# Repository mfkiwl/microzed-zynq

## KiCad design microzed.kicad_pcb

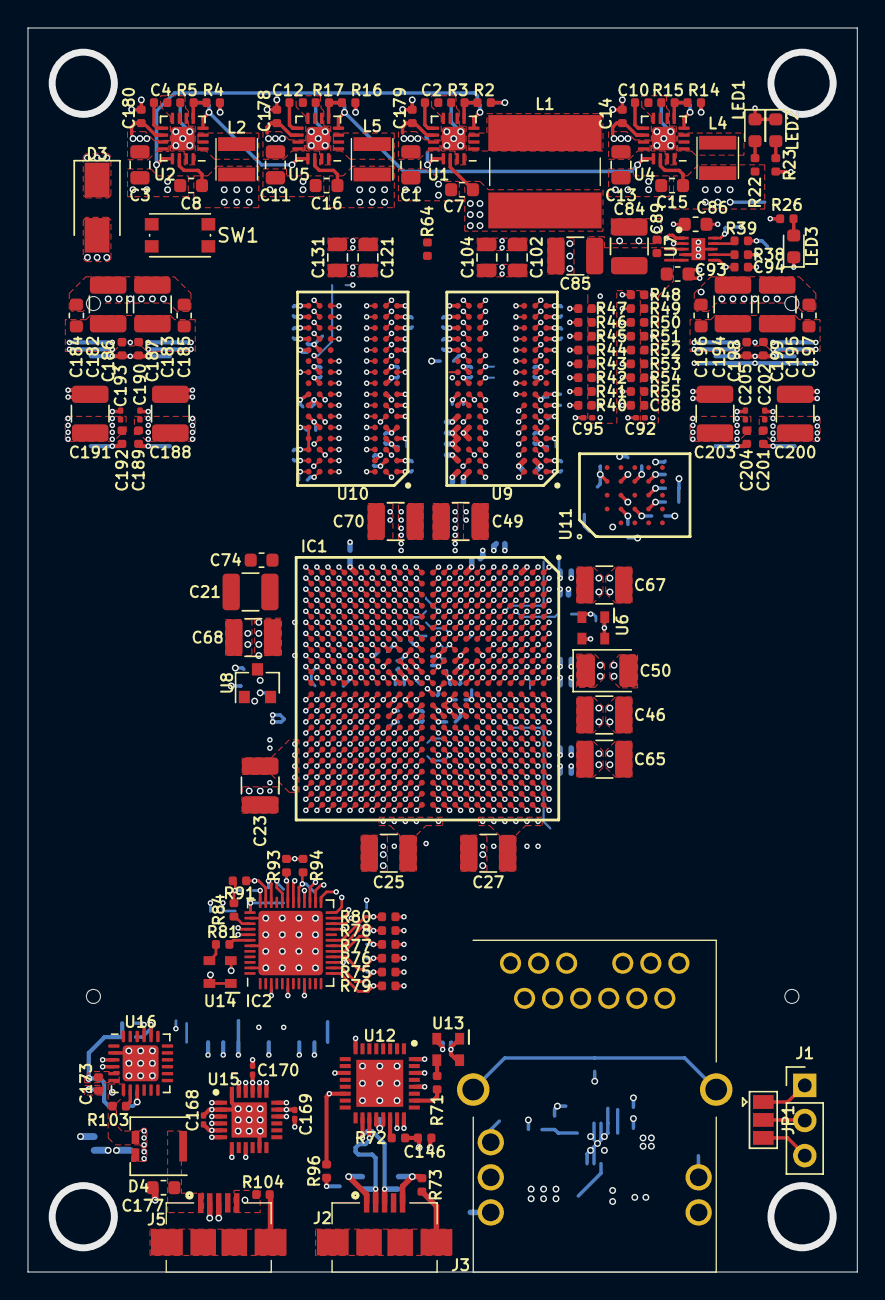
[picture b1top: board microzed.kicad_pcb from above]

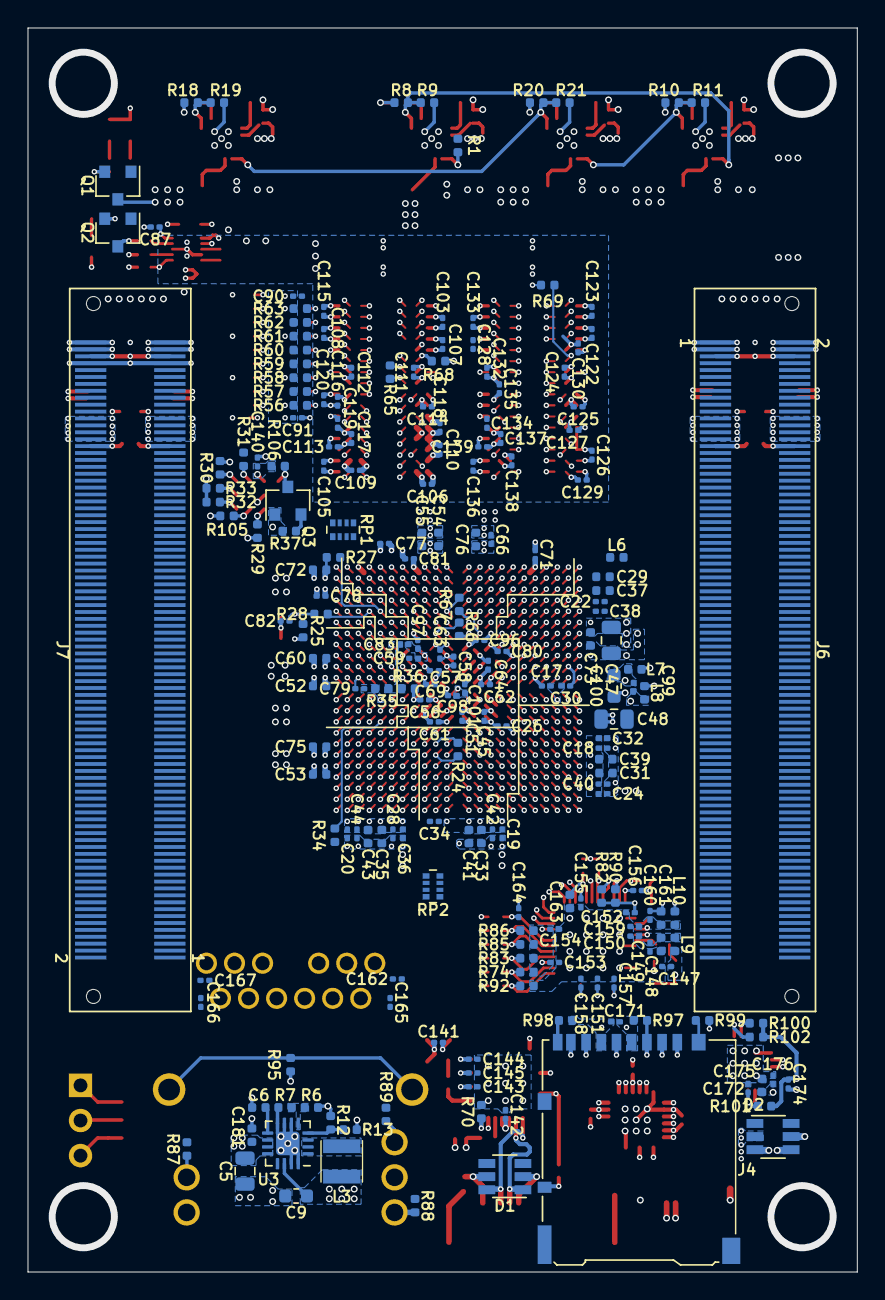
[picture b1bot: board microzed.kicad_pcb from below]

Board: 10 copper layers, 60.0 x 90.0 mm, 360 parts (210 on the bottom side), 440 nets.

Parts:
C1, C3, C5, C11, C13: 10µF; C_0805_2012Metric
C2, C4, C6, C10, C12: 3300pF; C_0402_1005Metric
C7, C8, C9, C15, C16: 22µF; C_0603_1608Metric
C14, C178, C179, C180, C181, C186, C187, C198, C199: 0.1µF; C_0402_1005Metric
C17, C18, C19, C20, C22, C24, C26, C28, C30, C32, C34, C36, C38, C40, C42, C44, C45, C51, C56, C57, C58, C59, C61, C62, C63, C64, C66, C69, C71, C77, C78, C79, C80, C81, C99: 0.47µF; C_0201_0603Metric
C21, C23, C25, C27, C46, C49, C65, C67, C68, C70, C84, C85, C182, C183, C188, C191, C194, C195, C200, C203: 100µF; C_1210_3225Metric
C29, C31, C33, C35, C37, C39, C41, C43, C52, C53, C54, C55, C60, C72, C73, C75, C76, C88, C89, C146, C148, C161, C173, C175, C189, C192, C201, C204: 4.7µF; C_0402_1005Metric
C47, C48, C102, C104, C121, C131: 47µF; C_0805_2012Metric
C50: 330µF; CP_EIA-3528-21_Kemet-B
C74, C86, C93, C100: 10µF; C_0603_1608Metric
C82, C87, C90, C91, C98, C101, C106, C108, C110, C112, C114, C116, C118, C119, C123, C125, C127, C129, C133, C135, C137, C139, C140, C141, C142, C143, C144, C145, C147, C149, C150, C151, C152, C153, C154, C155, C156, C157, C158, C159, C160, C162, C165, C166, C167, C168, C169, C170, C171, C172, C174, C176, C190, C193, C202, C205: 0.1µF; C_0201_0603Metric
C83, C92, C95, C96, C97, C103, C105, C107, C109, C111, C113, C115, C117, C120, C122, C124, C126, C128, C130, C132, C134, C136, C138: 0.01µF; C_0201_0603Metric
C94: 0.22µF; C_0402_1005Metric
C163: 1µF; C_0402_1005Metric
C164: 10pF; C_0201_0603Metric
C177, C184, C185, C196, C197: 2.2µF; C_0603_1608Metric
D1, D2: CDSOT23-SR208; TSOT-23-6
D3: B330; D_SMA
D4: ZEN056V130A24LS; Littelfuse_PolyZen-LS
IC1: XC7Z020-1CLG484C; BGA-484_19.0x19.0mm_Layout22x22_P0.8mm
IC2: RTL8211E-VL-CG; QFN-48-1EP_6x6mm_P0.4mm_EP4.66x4.66mm
J1: 640456-3; PinHeader_1x03_P2.54mm_Vertical
J2, J5: 10104111-0001LF; MICRO_USB_AB_TYPE_RECEPTACLE
J3: L829-1J1T-43; L8291J1T43
J4: Micro_SD_Card_Det_Hirose_DM3AT; microSD_HC_Hirose_DM3AT-SF-PEJM5
J6, J7: BSH-090-01-X-D-A
JP1: Jumper_3_Open; SolderJumper-3_P1.3mm_Open_Pad1.0x1.5mm
L1: 2.2µH; SRN8040
L2, L3, L4, L5: 1.0µH; SRN3015
L6, L7, L8, L9, L10: 220Ω@100MHz; L_0402_1005Metric
LED1, LED2, LED3: Blue; LED_0603_1608Metric
Q1, Q2: MMBT3904; SOT-23
Q3: BSS138; SOT-23
R1, R35, R36, R37, R38, R39, R96, R97, R100, R102: 10k; R_0402_1005Metric
R2, R10, R12, R15, R20: 76.8k; R_0402_1005Metric
R3, R4, R9, R11, R13, R17, R19, R21: 300k; R_0402_1005Metric
R5, R14: 240k; R_0402_1005Metric
R6: 226k; R_0402_1005Metric
R7: 43k; R_0402_1005Metric
R8, R18, R23, R25, R26, R34, R40, R41, R42, R43, R44, R45, R46, R47, R48, R49, R50, R51, R52, R53, R54, R55, R56, R57, R58, R59, R60, R61, R62, R63, R71, R81: 40.2; R_0402_1005Metric
R16: 205k; R_0402_1005Metric
R22, R68, R69, R87, R88, R89: 240; R_0402_1005Metric
R24, R72: 1k; R_0402_1005Metric
R27, R28, R29, R30, R31, R32, R33: 20K; R_0402_1005Metric
R64, R74, R82, R83, R85, R86, R90, R91, R92, R94, R101: 4.7k; R_0402_1005Metric
R65, R66, R67: 80.6; R_0402_1005Metric
R70: 8.06k 1%; R_0402_1005Metric
R73, R95, R98, R99, R104: 0; R_0402_1005Metric
R75, R76, R77, R78, R79, R80: 22; R_0402_1005Metric
R84: 2.49k 1%; R_0402_1005Metric
R93: 1.5k; R_0402_1005Metric
R103: 100; R_0402_1005Metric
R105, R106: 10K; R_0402_1005Metric
RP1: 10k; R_Array_Convex_4x0402
RP2: 4.7k; R_Array_Convex_4x0402
SW1: SW_Push; SW_Push_1P1T_NO_CK_KMR2
U1, U2, U3, U4, U5: TLV62130RGTR; QFN-16-1EP_3x3mm_P0.5mm_EP1.7x1.7mm
U6: ASDMB-33.333MHZ-LC-T; ABRACON-ASDMB
U7: TPS51206DSQR; SON40P200X200X80-11N
U8: REF3012; SOT-23
U9, U10: MT41K256M16TW; BGA-96_8.0x14.0mm_Layout2x3x16_P0.8mm
U11: MT25QL128ABA8E12-1SIT; BGA-24_6.0x8.0mm_Layout5x5_P1.0mm
U12: USB3320C-EZK; QFN50P500X500X100-33N-D
U13: ASDMB-24.000MHZ-LC-T; ABRACON-ASDMB
U14: ASDMB-25.000MHZ-LC-T; ABRACON-ASDMB
U15: TXS02612RTWR; QFN50P400X400X80-25N-D
U16: CP2104-F03-GM; QFN-24-1EP_4x4mm_P0.5mm_EP2.6x2.6mm

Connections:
5V_EN: U3.13, U12.17
+5V: C9.1, C146.1, D1.2, J2.1, L3.2, R6.1, R12.1, R72.1, U3.14
/BANK500/PS_MIO0: IC1.G6, Q2.1
/BANK500/PS_MIO7: IC1.D5, R28.1
/BANK500/PS_MIO8: IC1.E5, R27.2
/BANK502/DDR3_VTT: C84.1, C85.1, C88.1, C89.1, C90.1, C91.1, C92.1, C93.1, C95.1, R40.1, R41.1, R42.1, R43.1, R44.1, R45.1, R46.1, R47.1, R48.1, R49.1, R50.1, R51.1, R52.1, R53.1, R54.1, R55.1, R56.1, R57.1, R58.1, R59.1, R60.1, R61.1, R62.1, R63.1, U7.3, U7.5
/ethernet/AN0: IC2.17, R77.2, R85.1
/ethernet/AN1: IC2.18, R78.2, R86.1
/ethernet/ETH_AVDD10: C157.1, C158.1, C159.1, C160.1, C161.1, IC2.3, IC2.9, IC2.40, L10.2
/ethernet/ETH_AVDD33: C148.1, C149.1, C150.1, C151.1, IC2.6, IC2.41, L9.2
/ethernet/PHY_AD0: IC2.34, R87.2, R90.1
/ethernet/PHY_AD1: IC2.35, R88.2, R91.1
/ethernet/PHY_AD2: IC2.13, R79.2, R92.1
/ethernet/RXC: C164.2, IC2.19, R80.2
/ethernet/RXDLY: IC2.32, R82.1, R89.2
/ethernet/SELRGV: IC2.14, R74.1, R75.2
/ethernet/TXDLY: IC2.16, R76.2, R83.1
/pwrcvt/PG_1V: R8.2, R9.1, U1.4, U2.13
/pwrcvt/PG_1V35: R20.2, R21.1, U4.13, U5.4
/pwrcvt/PG_5V: R12.2, R13.1, U3.4
/usb-uart/USB2_N: D2.3, J5.2, U16.4
/usb-uart/USB2_P: D2.4, J5.3, U16.3
BANK13_LVDS_1_N: IC1.V9, J6.99
BANK13_LVDS_1_P: IC1.V10, J6.101
BANK13_LVDS_2_N: IC1.W8, J6.100
BANK13_LVDS_2_P: IC1.V8, J6.102
BANK13_LVDS_3_N: IC1.W10, J6.93
BANK13_LVDS_3_P: IC1.W11, J6.95
BANK13_LVDS_4_N: IC1.W12, J6.94
BANK13_LVDS_4_P: IC1.V12, J6.96
BANK13_LVDS_5_N: IC1.U11, J6.87
BANK13_LVDS_5_P: IC1.U12, J6.89
BANK13_LVDS_6_N: IC1.U9, J6.88
BANK13_LVDS_6_P: IC1.U10, J6.90
BANK13_LVDS_7_N: IC1.AB12, J6.81
BANK13_LVDS_7_P: IC1.AA12, J6.83
BANK13_LVDS_8_N: IC1.AB11, J6.82
BANK13_LVDS_8_P: IC1.AA11, J6.84
BANK13_LVDS_9_N: IC1.AB9, J6.75
BANK13_LVDS_9_P: IC1.AB10, J6.77
BANK13_LVDS_10_N: IC1.Y10, J6.76
BANK13_LVDS_10_P: IC1.Y11, J6.78
BANK13_LVDS_11_N: IC1.AA8, J6.69
BANK13_LVDS_11_P: IC1.AA9, J6.71
BANK13_LVDS_12_N: IC1.Y8, J6.70
BANK13_LVDS_12_P: IC1.Y9, J6.72
BANK13_LVDS_13_N: IC1.Y5, J6.63
BANK13_LVDS_13_P: IC1.Y6, J6.65
BANK13_LVDS_14_N: IC1.AA6, J6.64
BANK13_LVDS_14_P: IC1.AA7, J6.66
BANK13_LVDS_15_N: IC1.AB1, J6.57
BANK13_LVDS_15_P: IC1.AB2, J6.59
BANK13_LVDS_16_N: IC1.AB4, J6.58
BANK13_LVDS_16_P: IC1.AB5, J6.60
BANK13_LVDS_17_N: IC1.AB6, J6.51
BANK13_LVDS_17_P: IC1.AB7, J6.53
BANK13_LVDS_18_N: IC1.AA4, J6.52
BANK13_LVDS_18_P: IC1.Y4, J6.54
BANK13_LVDS_19_N: IC1.T6, J6.45
BANK13_LVDS_19_P: IC1.R6, J6.47
BANK13_LVDS_20_N: IC1.U4, J6.46
BANK13_LVDS_20_P: IC1.T4, J6.48
BANK13_LVDS_21_N: IC1.V4, J6.39
BANK13_LVDS_21_P: IC1.V5, J6.41
BANK13_LVDS_22_N: IC1.U5, J6.40
BANK13_LVDS_22_P: IC1.U6, J6.42
BANK13_LVDS_23_N: IC1.W7, J6.33
BANK13_LVDS_23_P: IC1.V7, J6.35
BANK13_LVDS_24_N: IC1.W5, J6.34
BANK13_LVDS_24_P: IC1.W6, J6.36
BANK13_SE_0: IC1.R7, J6.105
BANK13_SE_25: IC1.U7, J6.106
BANK33_LVDS_1_N: IC1.U21, J6.180
BANK33_LVDS_1_P: IC1.T21, J6.178
BANK33_LVDS_2_N: IC1.U22, J6.179
BANK33_LVDS_2_P: IC1.T22, J6.177
BANK33_LVDS_3_N: IC1.W22, J6.174
BANK33_LVDS_3_P: IC1.V22, J6.172
BANK33_LVDS_4_N: IC1.W21, J6.173
BANK33_LVDS_4_P: IC1.W20, J6.171
BANK33_LVDS_5_N: IC1.V20, J6.168
BANK33_LVDS_5_P: IC1.U20, J6.166
BANK33_LVDS_6_N: IC1.V19, J6.167
BANK33_LVDS_6_P: IC1.V18, J6.165
BANK33_LVDS_7_N: IC1.AB22, J6.162
BANK33_LVDS_7_P: IC1.AA22, J6.160
BANK33_LVDS_8_N: IC1.AB21, J6.161
BANK33_LVDS_8_P: IC1.AA21, J6.159
BANK33_LVDS_9_N: IC1.Y21, J6.156
BANK33_LVDS_9_P: IC1.Y20, J6.154
BANK33_LVDS_10_N: IC1.AB20, J6.155
BANK33_LVDS_10_P: IC1.AB19, J6.153
BANK33_LVDS_11_N: IC1.AA19, J6.150
BANK33_LVDS_11_P: IC1.Y19, J6.148
BANK33_LVDS_12_N: IC1.AA18, J6.149
BANK33_LVDS_12_P: IC1.Y18, J6.147
BANK33_LVDS_13_N: IC1.W18, J6.144
BANK33_LVDS_13_P: IC1.W17, J6.142
BANK33_LVDS_14_N: IC1.Y16, J6.143
BANK33_LVDS_14_P: IC1.W16, J6.141
BANK33_LVDS_15_N: IC1.U16, J6.138
BANK33_LVDS_15_P: IC1.U15, J6.136
BANK33_LVDS_16_N: IC1.V17, J6.137
BANK33_LVDS_16_P: IC1.U17, J6.135
BANK33_LVDS_17_N: IC1.AB17, J6.132
BANK33_LVDS_17_P: IC1.AA17, J6.130
BANK33_LVDS_18_N: IC1.AB16, J6.131
BANK33_LVDS_18_P: IC1.AA16, J6.129
BANK33_LVDS_19_N: IC1.V15, J6.126
BANK33_LVDS_19_P: IC1.V14, J6.124
BANK33_LVDS_20_N: IC1.W13, J6.125
BANK33_LVDS_20_P: IC1.V13, J6.123
BANK33_LVDS_21_N: IC1.Y15, J6.120
BANK33_LVDS_21_P: IC1.W15, J6.118
BANK33_LVDS_22_N: IC1.AA14, J6.119
BANK33_LVDS_22_P: IC1.Y14, J6.117
BANK33_LVDS_23_N: IC1.AA13, J6.114
BANK33_LVDS_23_P: IC1.Y13, J6.112
BANK33_LVDS_24_N: IC1.AB15, J6.113
BANK33_LVDS_24_P: IC1.AB14, J6.111
BANK33_SE_0: IC1.U19, J6.107
BANK33_SE_25: IC1.U14, J6.108
BANK34_LVDS_1_N: IC1.K15, J7.67
BANK34_LVDS_1_P: IC1.J15, J7.69
BANK34_LVDS_2_N: IC1.J17, J7.68
BANK34_LVDS_2_P: IC1.J16, J7.70
BANK34_LVDS_3_N: IC1.L16, J7.62
BANK34_LVDS_3_P: IC1.K16, J7.64, R24.2
BANK34_LVDS_4_N: IC1.M17, J7.61
BANK34_LVDS_4_P: IC1.L17, J7.63
BANK34_LVDS_5_N: IC1.N18, J7.56
BANK34_LVDS_5_P: IC1.N17, J7.58
BANK34_LVDS_6_N: IC1.M16, J7.55
BANK34_LVDS_6_P: IC1.M15, J7.57
BANK34_LVDS_7_N: IC1.K18, J7.50
BANK34_LVDS_7_P: IC1.J18, J7.52
BANK34_LVDS_8_N: IC1.J22, J7.49
BANK34_LVDS_8_P: IC1.J21, J7.51
BANK34_LVDS_9_N: IC1.K21, J7.44
BANK34_LVDS_9_P: IC1.J20, J7.46
BANK34_LVDS_10_N: IC1.L22, J7.43
BANK34_LVDS_10_P: IC1.L21, J7.45
BANK34_LVDS_11_N: IC1.K20, J7.38
BANK34_LVDS_11_P: IC1.K19, J7.40
BANK34_LVDS_12_N: IC1.L19, J7.37
BANK34_LVDS_12_P: IC1.L18, J7.39
BANK34_LVDS_13_N: IC1.M20, J7.32
BANK34_LVDS_13_P: IC1.M19, J7.34
BANK34_LVDS_14_N: IC1.N20, J7.31
BANK34_LVDS_14_P: IC1.N19, J7.33
BANK34_LVDS_15_N: IC1.M22, J7.26
BANK34_LVDS_15_P: IC1.M21, J7.28
BANK34_LVDS_16_N: IC1.P22, J7.25
BANK34_LVDS_16_P: IC1.N22, J7.27
BANK34_LVDS_17_N: IC1.R21, J7.20
BANK34_LVDS_17_P: IC1.R20, J7.22
BANK34_LVDS_18_N: IC1.P21, J7.19
BANK34_LVDS_18_P: IC1.P20, J7.21
BANK34_LVDS_19_N: IC1.P15, J7.14
BANK34_LVDS_19_P: IC1.N15, J7.16
BANK34_LVDS_20_N: IC1.P18, J7.13
BANK34_LVDS_20_P: IC1.P17, J7.15
BANK34_LVDS_21_N: IC1.T17, J7.8
BANK34_LVDS_21_P: IC1.T16, J7.10
BANK34_LVDS_22_N: IC1.T19, J7.7
BANK34_LVDS_22_P: IC1.R19, J7.9
BANK34_LVDS_23_N: IC1.T18, J7.2
BANK34_LVDS_23_P: IC1.R18, J7.4
BANK34_LVDS_24_N: IC1.R16, J7.1
BANK34_LVDS_24_P: IC1.P16, J7.3
BANK34_SE_0: IC1.H15, J7.74
BANK34_SE_25: IC1.R15, J7.73
BANK35_LVDS_1_N: IC1.E16, J7.146
BANK35_LVDS_1_P: IC1.F16, J7.148
BANK35_LVDS_2_N: IC1.D17, J7.145
BANK35_LVDS_2_P: IC1.D16, J7.147
BANK35_LVDS_3_N: IC1.D15, J7.140
BANK35_LVDS_3_P: IC1.E15, J7.142
BANK35_LVDS_4_N: IC1.G16, J7.139
BANK35_LVDS_4_P: IC1.G15, J7.141
BANK35_LVDS_5_N: IC1.E18, J7.134
BANK35_LVDS_5_P: IC1.F18, J7.136
BANK35_LVDS_6_N: IC1.F17, J7.133
BANK35_LVDS_6_P: IC1.G17, J7.135
BANK35_LVDS_7_N: IC1.B15, J7.128
BANK35_LVDS_7_P: IC1.C15, J7.130
BANK35_LVDS_8_N: IC1.B17, J7.127
BANK35_LVDS_8_P: IC1.B16, J7.129
BANK35_LVDS_9_N: IC1.A17, J7.122
BANK35_LVDS_9_P: IC1.A16, J7.124
BANK35_LVDS_10_N: IC1.A19, J7.121
BANK35_LVDS_10_P: IC1.A18, J7.123
BANK35_LVDS_11_N: IC1.C18, J7.116
BANK35_LVDS_11_P: IC1.C17, J7.118
BANK35_LVDS_12_N: IC1.C19, J7.115
BANK35_LVDS_12_P: IC1.D18, J7.117
BANK35_LVDS_13_N: IC1.B20, J7.110
BANK35_LVDS_13_P: IC1.B19, J7.112
BANK35_LVDS_14_N: IC1.C20, J7.109
BANK35_LVDS_14_P: IC1.D20, J7.111
BANK35_LVDS_15_N: IC1.A22, J7.104
BANK35_LVDS_15_P: IC1.A21, J7.106
BANK35_LVDS_16_N: IC1.C22, J7.103
BANK35_LVDS_16_P: IC1.D22, J7.105
BANK35_LVDS_17_N: IC1.D21, J7.98
BANK35_LVDS_17_P: IC1.E21, J7.100
BANK35_LVDS_18_N: IC1.B22, J7.97
BANK35_LVDS_18_P: IC1.B21, J7.99
BANK35_LVDS_19_N: IC1.H20, J7.92
BANK35_LVDS_19_P: IC1.H19, J7.94
BANK35_LVDS_20_N: IC1.F19, J7.91
BANK35_LVDS_20_P: IC1.G19, J7.93
BANK35_LVDS_21_N: IC1.E20, J7.86
BANK35_LVDS_21_P: IC1.E19, J7.88
BANK35_LVDS_22_N: IC1.G21, J7.85
BANK35_LVDS_22_P: IC1.G20, J7.87
BANK35_LVDS_23_N: IC1.F22, J7.80
BANK35_LVDS_23_P: IC1.F21, J7.82
BANK35_LVDS_24_N: IC1.G22, J7.79
BANK35_LVDS_24_P: IC1.H22, J7.81
BANK35_SE_0: IC1.H17, J7.76
BANK35_SE_25: IC1.H18, J7.75
CARRIER_SRST#: IC1.C9, J6.14, Q3.2, R37.2, SW1.1
DDR3_A0: IC1.M4, R40.2, U9.N3, U10.N3
DDR3_A1: IC1.M5, R41.2, U9.P7, U10.P7
DDR3_A2: IC1.K4, R42.2, U9.P3, U10.P3
DDR3_A3: IC1.L4, R43.2, U9.N2, U10.N2
DDR3_A4: IC1.K6, R44.2, U9.P8, U10.P8
DDR3_A5: IC1.K5, R45.2, U9.P2, U10.P2
DDR3_A6: IC1.J7, R46.2, U9.R8, U10.R8
DDR3_A7: IC1.J6, R47.2, U9.R2, U10.R2
DDR3_A8: IC1.J5, R48.2, U9.T8, U10.T8
DDR3_A9: IC1.H5, R49.2, U9.R3, U10.R3
DDR3_A10: IC1.J3, R50.2, U9.L7, U10.L7
DDR3_A11: IC1.G5, R51.2, U9.R7, U10.R7
DDR3_A12: IC1.H4, R52.2, U9.N7, U10.N7
DDR3_A13: IC1.F4, R53.2, U9.T3, U10.T3
DDR3_A14: IC1.G4, R54.2, U9.T7, U10.T7
DDR3_BA0: IC1.L7, R55.2, U9.M2, U10.M2
DDR3_BA1: IC1.L6, R56.2, U9.N8, U10.N8
DDR3_BA2: IC1.M6, R57.2, U9.M3, U10.M3
DDR3_CAS#: IC1.P3, R60.2, U9.K3, U10.K3
DDR3_CKE: IC1.V3, R63.2, U9.K9, U10.K9
DDR3_CK_N: IC1.N5, R65.2, U9.K7, U10.K7
DDR3_CK_P: IC1.N4, R65.1, U9.J7, U10.J7
DDR3_CS#: IC1.P6, R58.2, U9.L2, U10.L2
DDR3_DM0: IC1.B1, U9.E7
DDR3_DM1: IC1.H3, U9.D3
DDR3_DM2: IC1.P1, U10.E7
DDR3_DM3: IC1.AA2, U10.D3
DDR3_DQ0: IC1.D1, U9.E3
DDR3_DQ1: IC1.C3, U9.F7
DDR3_DQ2: IC1.B2, U9.F2
DDR3_DQ3: IC1.D3, U9.F8
DDR3_DQ4: IC1.E3, U9.H3
DDR3_DQ5: IC1.E1, U9.H8
DDR3_DQ6: IC1.F2, U9.G2
DDR3_DQ7: IC1.F1, U9.H7
DDR3_DQ8: IC1.G2, U9.D7
DDR3_DQ9: IC1.G1, U9.C3
DDR3_DQ10: IC1.L1, U9.C8
DDR3_DQ11: IC1.L2, U9.C2
DDR3_DQ12: IC1.L3, U9.A7
DDR3_DQ13: IC1.K1, U9.A2
DDR3_DQ14: IC1.J1, U9.B8
DDR3_DQ15: IC1.K3, U9.A3
DDR3_DQ16: IC1.M1, U10.E3
DDR3_DQ17: IC1.T3, U10.F7
DDR3_DQ18: IC1.N3, U10.F2
DDR3_DQ19: IC1.T1, U10.F8
DDR3_DQ20: IC1.R3, U10.H3
DDR3_DQ21: IC1.T2, U10.H8
DDR3_DQ22: IC1.M2, U10.G2
DDR3_DQ23: IC1.R1, U10.H7
DDR3_DQ24: IC1.AA3, U10.D7
DDR3_DQ25: IC1.U1, U10.C3
DDR3_DQ26: IC1.AA1, U10.C8
DDR3_DQ27: IC1.U2, U10.C2
DDR3_DQ28: IC1.W1, U10.A7
DDR3_DQ29: IC1.Y3, U10.A2
DDR3_DQ30: IC1.W3, U10.B8
DDR3_DQ31: IC1.Y1, U10.A3
DDR3_DQS0_N: IC1.D2, U9.G3
DDR3_DQS0_P: IC1.C2, U9.F3
DDR3_DQS1_N: IC1.J2, U9.B7
DDR3_DQS1_P: IC1.H2, U9.C7
DDR3_DQS2_N: IC1.P2, U10.G3
DDR3_DQS2_P: IC1.N2, U10.F3
DDR3_DQS3_N: IC1.W2, U10.B7
DDR3_DQS3_P: IC1.V2, U10.C7
DDR3_ODT: IC1.P5, R62.2, U9.K1, U10.K1
DDR3_RAS#: IC1.R5, R61.2, U9.J3, U10.J3
DDR3_RST#: IC1.F3, R64.2, U9.T2, U10.T2
DDR3_WE#: IC1.R4, R59.2, U9.L3, U10.L3
ETH_INT: IC1.C14, IC2.20
ETH_MDC: IC1.D10, IC2.30
ETH_MDIO: IC1.C12, IC2.31, R93.1
ETH_RST#: C163.1, IC1.D11, IC2.29, R94.1
ETH_RX_CLK: IC1.A14, R80.1
ETH_RX_CTRL: IC1.D7, R79.1
ETH_RX_D0: IC1.E11, R75.1
ETH_RX_D1: IC1.B7, R76.1
ETH_RX_D2: IC1.F12, R77.1
ETH_RX_D3: IC1.A13, R78.1
ETH_TX_CLK: IC1.D6, IC2.22
ETH_TX_CTRL: IC1.F11, IC2.27
ETH_TX_D0: IC1.E9, IC2.23
ETH_TX_D1: IC1.A7, IC2.24
ETH_TX_D2: IC1.E10, IC2.25
ETH_TX_D3: IC1.A8, IC2.26
FPGA_DONE: IC1.T12, J7.169, Q1.1
GND: C1.2, C2.2, C3.2, C4.2, C5.2, C6.2, C7.2, C8.2, C9.2, C10.2, C11.2, C12.2, C13.2, C14.1, C15.2, C16.2, C17.2, C18.2, C19.2, C20.2, C21.2, C22.2, C23.2, C24.2, C25.2, C26.2, C27.2, C28.2, C29.2, C30.2, C31.2, C32.2, C33.2, C34.2, C35.2, C36.2, C37.2, C38.2, C39.2, C40.2, C41.2, C42.2, C43.2, C44.2, C45.2, C46.2, C47.2, C48.2, C49.2, C50.2, C51.2, C52.2, C53.2, C54.2, C55.2, C56.2, C57.2, C58.2, C59.2, C60.2, C61.2, C62.2, C63.2, C64.2, C65.2, C66.2, C67.2, C68.2, C69.2, C70.2, C71.2, C72.2, C73.2, C74.2, C75.2, C76.2, C77.2, C78.2, C79.2, C80.2, C81.2, C82.2, C83.2, C84.2, C85.2, C86.2, C87.2, C88.2, C89.2, C90.2, C91.2, C92.2, C93.2, C94.2, C95.2, C96.2, C97.2, C102.2, C103.2, C104.2, C105.2, C106.2, C107.2, C108.2, C109.2, C110.2, C111.2, C112.2, C113.2, C114.2, C115.2, C116.2, C117.2, C118.2, C119.2, C120.2, C121.2, C122.2, C123.2, C124.2, C125.2, C126.2, C127.2, C128.2, C129.2, C130.2, C131.2, C132.2, C133.2, C134.2, C135.2, C136.2, C137.2, C138.2, C139.2, C140.2, C141.2, C142.2, C143.2, C144.2, C145.2, C146.2, C147.2, C148.2, C149.2, C150.2, C151.2, C152.2, C153.2, C154.2, C155.2, C156.2, C157.2, C158.2, C159.2, C160.2, C161.2, C162.2, C163.2, C164.1, C165.2, C166.2, C167.2, C168.2, C169.2, C170.2, C171.2, C172.2, C173.2, C174.2, C175.2, C176.2, C177.2, C178.1, C179.1, C180.1, C181.1, C182.2, C183.2, C184.2, C185.2, C186.2, C187.2, C188.2, C189.2, C190.2, C191.2, C192.2, C193.2, C194.2, C195.2, C196.2, C197.2, C198.2, C199.2, C200.2, C201.2, C202.2, C203.2, C204.2, C205.2, D1.5, D2.5, D4.2, IC1.A5, IC1.A15, IC1.AA5, IC1.AA15, IC1.AB8, IC1.AB18, IC1.B8, IC1.B18, IC1.C1, IC1.C11, IC1.C21, IC1.D4, IC1.D14, IC1.E7, IC1.E17, IC1.F10, IC1.F20, IC1.G3, IC1.H6, IC1.H8, IC1.H12, IC1.H14, IC1.H16, IC1.J9, IC1.J11, IC1.J13, IC1.J19, IC1.K2, IC1.K8, IC1.K10, IC1.K14, IC1.K22, IC1.L5, IC1.L9, IC1.L13, IC1.L15, IC1.M8, IC1.M10, IC1.M14, IC1.M18, IC1.N1, IC1.N9, IC1.N11, IC1.N12, IC1.N13, IC1.N21, IC1.P4, IC1.P8, IC1.P10, IC1.P12, IC1.P14, IC1.R9, IC1.R11, IC1.R13, IC1.R17, IC1.T20, IC1.U3, IC1.U13, IC1.V6, IC1.V16, IC1.W9, IC1.W19, IC1.Y2, IC1.Y12, IC1.Y22, IC2.38, IC2.43, IC2.47, IC2.49, J1.3, J2.5, J4.6, J5.5, J6.5, J6.6, J6.11, J6.12, J6.31, J6.32, J6.37, J6.38, J6.43, J6.44, J6.49, J6.50, J6.55, J6.56, J6.61, J6.62, J6.67, J6.68, J6.73, J6.74, J6.79, J6.80, J6.85, J6.86, J6.91, J6.92, J6.97, J6.98, J6.103, J6.104, J6.109, J6.110, J6.115, J6.116, J6.121, J6.122, J6.127, J6.128, J6.133, J6.134, J6.139, J6.140, J6.145, J6.146, J6.151, J6.152, J6.157, J6.158, J6.163, J6.164, J6.169, J6.170, J6.175, J6.176, J7.5, J7.6, J7.11, J7.12, J7.17, J7.18, J7.23, J7.24, J7.29, J7.30, J7.35, J7.36, J7.41, J7.42, J7.47, J7.48, J7.53, J7.54, J7.59, J7.60, J7.65, J7.66, J7.71, J7.72, J7.77, J7.78, J7.83, J7.84, J7.89, J7.90, J7.95, J7.96, J7.101, J7.102, J7.107, J7.108, J7.113, J7.114, J7.119, J7.120, J7.125, J7.126, J7.131, J7.132, J7.137, J7.138, J7.143, J7.144, J7.149, J7.150, J7.168, J7.175, J7.176, JP1.3, L7.1, LED1.1, LED2.1, LED3.1, R3.2, R5.2, R7.2, R9.2, R11.2, R13.2, R15.2, R17.2, R19.2, R21.2, R28.2, R29.2, R32.2, R33.2, R36.2, R64.1, R67.1, R68.2, R69.2, R70.2, R73.2, R84.2, R91.2, R92.2, R95.1, R98.2, R99.2, R104.2, SW1.2, U1.6, U1.7, U1.8, U1.15, U1.16, U1.17, U2.6, U2.7, U2.8, U2.15, U2.16, U2.17, U3.6, U3.7, U3.8, U3.15, U3.16, U3.17, U4.6, U4.7, U4.8, U4.15, U4.16, U4.17, U5.6, U5.7, U5.8, U5.15, U5.16, U5.17, U6.2, U7.4, U7.8, U7.11, U9.A9, U9.B1, U9.B3, U9.B9, U9.D1, U9.D8, U9.E1, U9.E2, U9.E8, U9.F9, U9.G1, U9.G8, U9.G9, U9.J2, U9.J8, U9.M1, U9.M9, U9.P1, U9.P9, U9.T1, U9.T9, U10.A9, U10.B1, U10.B3, U10.B9, U10.D1, U10.D8, U10.E1, U10.E2, U10.E8, U10.F9, U10.G1, U10.G8, U10.G9, U10.J2, U10.J8, U10.M1, U10.M9, U10.P1, U10.P9, U10.T1, U10.T9, U11.B3, U12.33, U13.2, U14.2, U15.2, U15.11, U15.24, U15.25, U16.2, U16.25
GNDADC: C98.2, C99.2, C100.2, C101.2, IC1.K12, IC1.L12, L7.2, U8.3
GNDPWR: J2.6, J2.7, J2.8, J2.9, J3.18, J3.19, J4.11, J5.6, J5.7, J5.8, J5.9, R73.1, R95.2, R99.1, R104.1
JTAG_TCK: IC1.G11, J7.164, RP1.6
JTAG_TDI: IC1.H13, J7.162, RP1.7
JTAG_TDO: IC1.G14, J7.160, RP1.8
JTAG_TMS: IC1.G12, J7.166, RP1.5
unnamed: C2.1, U1.9
unnamed: C4.1, U2.9
unnamed: C6.1, U3.9
unnamed: C10.1, U4.9
unnamed: C12.1, U5.9
unnamed: C83.1, IC1.F8, R35.2, R36.1
unnamed: C162.1, C165.1, C166.1, C167.1, J3.1, J3.6, J3.7, J3.12
unnamed: C172.1, R101.2, U16.9
unnamed: C173.1, C174.1, R100.1, R101.1, R102.1, U16.5, U16.6
unnamed: C175.1, C176.1, D2.2, D3.2, D4.3, R103.2, U16.7
unnamed: C177.1, D4.1, J5.1
unnamed: D1.1, J2.2, U12.19
unnamed: D1.6, J2.3, U12.18
unnamed: IC1.E14, R34.2
unnamed: IC1.F7, R25.2
unnamed: IC1.M7, R66.2
unnamed: IC1.N7, R67.2
unnamed: IC1.T11, RP2.2
unnamed: IC1.T13, RP2.4
unnamed: IC1.T14, RP2.3
unnamed: IC2.1, J3.11
unnamed: IC2.2, J3.10
unnamed: IC2.4, J3.4
unnamed: IC2.5, J3.5
unnamed: IC2.7, J3.3
unnamed: IC2.8, J3.2
unnamed: IC2.10, J3.8
unnamed: IC2.11, J3.9
unnamed: IC2.39, R84.1
unnamed: IC2.42, R81.2
unnamed: J1.2, JP1.2, R31.2
unnamed: J2.4, U12.23
unnamed: J3.13, R87.1
unnamed: J3.15, R89.1
unnamed: J3.17, R88.1
unnamed: J4.1, U15.23
unnamed: J4.2, U15.22
unnamed: J4.3, R97.2, U15.20
unnamed: J4.5, U15.19
unnamed: J4.7, U15.18
unnamed: J4.8, U15.16
unnamed: J4.9, R98.1
unnamed: L1.1, U1.1, U1.2, U1.3
unnamed: L2.1, U2.1, U2.2, U2.3
unnamed: L3.1, U3.1, U3.2, U3.3
unnamed: L4.1, U4.1, U4.2, U4.3
unnamed: L5.1, U5.1, U5.2, U5.3
unnamed: LED1.2, R22.1
unnamed: LED2.2, R23.2
unnamed: LED3.2, R26.2
unnamed: Q1.2, R23.1
unnamed: Q2.2, R26.1
unnamed: Q3.3, R106.2, U11.A4
unnamed: R2.2, R3.1, U1.5
unnamed: R4.2, R5.1, U2.5
unnamed: R6.2, R7.1, U3.5
unnamed: R14.2, R15.1, U4.5
unnamed: R16.2, R17.1, U5.5
unnamed: R25.1, U6.3
unnamed: R38.1, U7.7
unnamed: R39.1, U7.9
unnamed: R68.1, U9.L8
unnamed: R69.1, U10.L8
unnamed: R70.1, U12.24
unnamed: R71.1, U12.26
unnamed: R71.2, U13.3
unnamed: R72.2, U12.22
unnamed: R81.1, U14.3
unnamed: R103.1, U16.8
PG_1V8: J6.13, R10.2, R11.1, U2.4, U5.13
PG_MODULE: IC1.B5, J7.171, R18.2, R19.1, U4.4
PS_MIO9: IC1.C4, J7.167
PS_MIO10: IC1.G7, J7.165
PS_MIO11: IC1.B4, J7.163
PS_MIO12: IC1.C5, J7.161
PS_MIO13: IC1.A6, J7.159
PS_MIO50: IC1.C10, J6.15
PS_MIO51: IC1.D13, J6.17
PWR_B501: C8.1, C47.1, C53.1, C58.1, C62.1, C65.1, C68.1, C73.1, C75.1, C79.1, C80.1, C141.1, C143.1, C144.1, C145.1, C153.1, C154.1, C168.1, IC1.A10, IC1.B13, IC1.D9, IC1.E12, IC1.G9, IC1.K9, IC1.L10, IC1.M9, IC1.N10, IC1.P9, IC1.P11, IC1.R10, IC1.T9, IC2.15, IC2.21, J6.9, J6.10, L2.2, L6.1, L8.1, Q3.1, R4.1, R10.1, R35.1, R37.1, R74.2, R83.2, R85.2, R86.2, R93.2, R94.2, R96.1, U2.14, U12.8, U12.11, U12.14, U12.28, U12.30, U12.32, U13.1, U13.4, U15.5
PWR_EN: J6.7, R1.2, U1.13
QSPI_CS#: IC1.A1, R105.2, U11.C2
QSPI_DQ0: IC1.A2, R33.1, U11.D3
QSPI_DQ1: IC1.F6, R32.1, U11.D2
QSPI_DQ2: IC1.E4, R31.1, U11.C4
QSPI_DQ3: IC1.A3, R30.2, U11.D4
QSPI_SCK: IC1.A4, R29.1, U11.B2
SD_CD: IC1.D12, J4.10, R96.2
SD_CLK: R34.1, U15.9
SD_CMD: IC1.C8, U15.4
SD_D0: IC1.D8, U15.6
SD_D1: IC1.B11, U15.7
SD_D2: IC1.E13, U15.1
SD_D3: IC1.B9, U15.3
USB_CLK: IC1.A9, U12.1
USB_D0: IC1.C7, U12.3
USB_D1: IC1.G13, U12.4
USB_D2: IC1.B12, U12.5
USB_D3: IC1.F14, U12.6
USB_D4: IC1.A12, U12.7
USB_D5: IC1.B14, U12.9
USB_D6: IC1.F13, U12.10
USB_D7: IC1.C13, U12.13
USB_DIR: IC1.E8, U12.31
USB_NXT: IC1.F9, U12.2
USB_RST#: IC1.B10, U12.27
USB_STP: IC1.A11, U12.29
USB_UART_RxD: IC1.B6, R100.2, U16.21
USB_UART_TxD: IC1.E6, R102.2, U16.20
V3V3: C15.1, C48.1, C67.1, C72.1, C78.1, C82.1, C86.1, C87.1, C140.1, C142.1, C147.1, C152.1, C169.1, C170.1, C171.1, IC1.B3, IC1.C6, IC1.R12, IC1.T7, IC1.T8, IC1.T10, IC2.37, J1.1, J3.14, J3.16, J4.4, J7.173, J7.174, JP1.1, L4.2, L9.1, Q1.3, Q2.3, R14.1, R18.1, R22.2, R27.1, R30.1, R38.2, R39.2, R82.2, R90.2, R97.1, R105.1, R106.1, RP1.1, RP1.2, RP1.3, RP1.4, RP2.5, RP2.6, RP2.7, RP2.8, U4.14, U6.1, U6.4, U7.2, U7.10, U11.B4, U12.20, U12.21, U14.1, U14.4, U15.17, U15.21
VCCADC: C98.1, C99.1, IC1.K11, L8.2, U8.1
VCCBRAM: C7.1, C45.1, C46.1, C49.1, C50.1, C51.1, C52.1, C54.1, C55.1, C56.1, C57.1, C59.1, C60.1, C61.1, C63.1, C64.1, C155.1, C156.1, IC1.G8, IC1.H9, IC1.H11, IC1.J8, IC1.J10, IC1.J12, IC1.J14, IC1.K13, IC1.L8, IC1.L14, IC1.M13, IC1.N8, IC1.N14, IC1.P13, IC1.R8, IC1.R14, IC2.28, IC2.36, L1.2, L10.1, R2.1, R8.1, U1.14
VCCO_13: C17.1, C21.1, C22.1, C29.1, C30.1, C37.1, C38.1, C188.1, C189.1, C190.1, IC1.AA10, IC1.AB3, IC1.T5, IC1.U8, IC1.V11, IC1.W4, IC1.Y7, J6.23, J6.25, J6.27, J6.29
VCCO_33: C18.1, C23.1, C24.1, C31.1, C32.1, C39.1, C40.1, C191.1, C192.1, C193.1, IC1.AA20, IC1.AB13, IC1.U18, IC1.V21, IC1.W14, IC1.Y17, J6.24, J6.26, J6.28, J6.30
VCCO_34: C19.1, C25.1, C26.1, C33.1, C34.1, C41.1, C42.1, C200.1, C201.1, C202.1, IC1.K17, IC1.L20, IC1.N16, IC1.P19, IC1.R22, IC1.T15, J7.152, J7.154, J7.156, J7.158, R24.1
VCCO_35: C20.1, C27.1, C28.1, C35.1, C36.1, C43.1, C44.1, C203.1, C204.1, C205.1, IC1.A20, IC1.C16, IC1.D19, IC1.E22, IC1.F15, IC1.G18, IC1.H21, J7.151, J7.153, J7.155, J7.157
VCCO_DDR: C16.1, C66.1, C70.1, C71.1, C76.1, C77.1, C81.1, C102.1, C103.1, C104.1, C105.1, C106.1, C107.1, C108.1, C109.1, C110.1, C111.1, C112.1, C113.1, C114.1, C115.1, C116.1, C117.1, C118.1, C119.1, C121.1, C122.1, C123.1, C124.1, C125.1, C126.1, C127.1, C128.1, C129.1, C131.1, C132.1, C133.1, C134.1, C135.1, C136.1, C137.1, C138.1, C139.1, IC1.E2, IC1.F5, IC1.H1, IC1.J4, IC1.K7, IC1.M3, IC1.N6, IC1.R2, IC1.V1, L5.2, R16.1, R20.1, R66.1, U5.14, U7.1, U9.A1, U9.A8, U9.B2, U9.C1, U9.C9, U9.D2, U9.D9, U9.E9, U9.F1, U9.G7, U9.H2, U9.H9, U9.K2, U9.K8, U9.N1, U9.N9, U9.R1, U9.R9, U10.A1, U10.A8, U10.B2, U10.C1, U10.C9, U10.D2, U10.D9, U10.E9, U10.F1, U10.G7, U10.H2, U10.H9, U10.K2, U10.K8, U10.N1, U10.N9, U10.R1, U10.R9
VCCPLL: C69.1, C74.1, IC1.H10, L6.2
VIN: C1.1, C3.1, C5.1, C11.1, C13.1, C14.2, C178.2, C179.2, C180.2, C181.2, C182.1, C183.1, C184.1, C185.1, C186.1, C187.1, C194.1, C195.1, C196.1, C197.1, C198.1, C199.1, D3.1, J6.1, J6.2, J6.3, J6.4, J7.177, J7.178, J7.179, J7.180, R1.1, U1.10, U1.11, U1.12, U2.10, U2.11, U2.12, U3.10, U3.11, U3.12, U4.10, U4.11, U4.12, U5.10, U5.11, U5.12
VREFP: C100.1, C101.1, IC1.M11, U8.2
VTTREF: C94.1, C96.1, C97.1, C120.1, C130.1, IC1.H7, IC1.P7, U7.6, U9.H1, U9.M8, U10.H1, U10.M8
XADC0_N: IC1.M12, J7.170
XADC0_P: IC1.L11, J7.172

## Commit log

2018-08-20 init project
2018-08-21 add connector: 0821-1X1T-43-F
2018-08-21 0821-1X1T-43-F: update
2018-08-23 add new script 'genfp.sh' for generating footprint
2018-08-24 add Zynq7020 lib/footprint
2018-08-24 add source files
2018-08-27 add 3d model for xc7z020
2018-08-27 add 10104111-0001LF (microusb connector)
2018-08-27 add footprint/3d model for 10104111C
2018-08-28 script/fpcvt.sh: use tmp dir to avoid auto deletion by lib_convert.py
2018-08-28 add 5-146280-3
2018-08-28 add 3d model for 5-146280-3
2018-08-28 add 61082-101400LF
2018-08-28 add MT41K256M16HA-125_E_TR
2018-08-28 add 3d model for MT41K256M16HA-125_E_TR
2018-08-28 add 3d model for s61082-101x0xxx
2018-08-28 add 88E1512
2018-08-28 add BCS-106-X-D-TE
2018-08-28 add CDSOT23-SR208
2018-08-28 add CP2104-F03-GM
2018-08-28 add DSC1001DI1-024.0000
2018-08-29 add DSC1001DI1-033.3300
2018-09-04 add MT41K256M16HA-125_E / +0V75
2018-09-04 add TPS51206DSQR
2018-09-04 add 3d model for TPS51206DSQR
2018-09-04 add 'PWR_CMM'
2018-09-04 sch: page 1
2018-09-04 split ddr3 related schematic
2018-09-05 add GRM033R60J104KE19D
2018-09-05 sch: use global label
2018-09-06 ddr3 sch init done!
2018-09-06 assign ? element for ddr3
2018-09-06 rename ZYNQ_DDR3.sch to BANK502.sch
2018-09-06 add ASDMB
2018-09-06 add fp for ASDMB / add BANK500.sch
2018-09-07 update for BANK500
2018-09-07 add ASDMB-33.333MHZ-LC-T for BANK500
2018-09-07 add resources
2018-09-09 fix sym-lib-table to use relative path
2018-09-10 BANK500 done
2018-09-10 add NC7WZ07FHX
2018-09-10 add BANK501
2018-09-10 add BANK501 in top sch
2018-09-11 add sdcard voltage level translator
2018-09-12 BANK 501 done
2018-09-12 add BSS138-7-F / CP2104-F03-GM / TLV62130RGTR
2018-09-13 start USB-UART
2018-09-17 usb-uart progress
2018-09-17 usb uart sch done
2018-09-18 start usb 2.0 otg
2018-09-18 update 3d models to wrl
2018-09-20 add wrl files for 3d model
2018-09-21 update symbol of USB3320C-EZK
2018-09-25 add link for zybo
2018-09-25 add usb2.0.sch
2018-09-26 add TPS2051BDBVR
2018-09-26 update usb otg
2018-09-27 usb otg initial done
2018-09-28 add ASDMB-25.000MHZ-LC-T
2018-09-28 start ethernet
2018-09-30 ethernet done
2018-10-08 add BANK34_35 sch
2018-10-09 add SN74AHC1G08DBV
2018-10-16 start power
2018-10-17 zynq power sch done
2018-10-19 power converter done
2018-10-23 assign number for all units
2018-10-23 fix pin type for TPS51206DSQR
2018-10-24 utils.sh: process xxx-rescue
2018-10-24 remove DX_0_P/DX_0_N
2018-10-25 add REF3012
2018-10-25 update xadc circuit for precise voltage.
2018-10-29 add schematic for Z-Turn
2018-11-13 rearrange directory
2019-01-08 add xc7z020-1CLG484
2019-01-11 change to clg484
2019-01-16 check asdmb
2019-01-18 update ug585 and some text notes.
2019-01-24 check : usb2
2019-01-25 change tps2051b to tps2069d
2019-01-25 remove auto code
2019-01-28 add rtl8211e
2019-01-28 start ethernet module using rtl8211e
2019-01-28 update rtl8211e
2019-01-29 add rj45 socket: L829-1J1T-43
2019-01-29 use new rj45 socket: L829-1J1T-43
2019-01-30 BANK501 changed to 3.3V: ethernet/usb/uart/sdio
2019-01-31 fixed VIN: 5V
2019-01-31 add new page for connector
2019-02-01 add BSH connector
2019-02-20 add bsh-060/bsh-090
2019-02-21 use connector
2019-02-21 start footprint
2019-02-25 fix spell error
2019-02-25 add script for select resistor
2019-02-25 add model for some elements
2019-02-26 checkresistor: improve
2019-02-27 checkresistor: done
2019-02-28 resistor checker done: just for selecting resistors for som voltage source.
2019-03-05 checkresistor: add resistor sel for PG pin
2019-03-05 update footprint for power converter
2019-03-06 powercvt footprint done
2019-03-07 use micro sign but not geek letter
2019-03-07 BANK0 footprint done
2019-03-08 BANK34: PUDC_B pull-up, disable internal pull-up for SELECTIO.
2019-03-08 start footprint for BANK500
2019-03-09 fix MIO voltage selection (MIO7/MIO8)
2019-03-09 fix R_ARRAY to R_PACK
2019-03-10 BANK500 footprint done
2019-03-10 add accessory notes for jumper
2019-03-10 add DS191 for Zynq7000
2019-03-10 start BANK502 footprint
2019-03-12 power: change VCCO_DDR3 from 1.5V to 1.35V
2019-03-12 BANK500: remove resistor on standby pin of ASDMB change MIO8 to pull-up: prepare for 1.8V MIO group 1
2019-03-12 add BOM for picozed
2019-03-13 update lib: add MT41K256M16TW, add MT25QL128ABA8E12-1
2019-03-13 change qspi and ddr IC.
2019-03-13 remove usb-uart module, using usb2.0 to provide power for SOM.
2019-03-13 assign footprint for 22Ohm resistors
2019-03-14 improve ethernet for footprint
2019-03-15 restore usb-uart module
2019-03-18 change sd card slot: DM3AT-SF-PEJM5
2019-03-18 footprint init done
2019-03-19 update for initial ERC
2019-03-20 sdio: remove unused WP eth: add interrupt
2019-03-20 lib: BSH-xxx connector, change pin type to passive
2019-03-20 ERC fix
2019-03-21 fix ERC for connector's shield
2019-03-22 move uart from BANK501 to BANK500
2019-03-22 BANK501: changed to 1.8V
2019-03-22 rtl8211 changed to low-voltage version
2019-03-22 fix symbol for 150uF capacitor
2019-03-22 output PG_1V8, PG_MODULE
2019-03-22 start allocate connector pin
2019-03-28 pin allocate done
2019-03-28 usb2.0 use dc-dc 5v directly. adjust connector pin allocation.
2019-04-03 start pcb
2019-04-03 add zone for GND
2019-04-04 3.3V power
2019-04-07 pcb: remove filled zone
2019-04-08 pcb: power init done
2019-04-08 pcb: start memory
2019-04-09 fix footprint & 3d model for xc7z020-clg484. (pin pitch 1.0mm -> 0.8mm)
2019-04-09 misc update
2019-04-09 fix footprint for BGA-96/BGA-484
2019-04-09 pcb: start memory.
2019-04-09 relax via settings
2019-04-10 start DDR3 DQ[0-7]
2019-04-11 add some resources
2019-04-14 consider pin delay
2019-04-15 pcb: vtt power
2019-04-16 pcb: add terminate resistor for ddr3
2019-04-17 continue memory capacitor
2019-04-18 memory capacitor position done.
2019-04-18 fix footprint for ddr3
2019-04-18 start zynq power capacitors
2019-04-19 zynq power capacitors done. start power plane
2019-04-21 start ethernet related elements
2019-04-22 pcb: ethernet init done
2019-04-22 pcb: vttref capacitor done
2019-04-25 qspi reset: add level translator
2019-04-26 elements located nearly done
2019-04-27 check rj45 connector, try to find smaller footprint
2019-04-27 pcb: add 3d model for rj45 connector
2019-04-28 update 3d model
2019-04-28 realloc connector pins
2019-04-29 start connector power capacitors
2019-04-29 finish capacitors for connector power pins
2019-04-30 pcb: 3d model done
2019-05-04 start connections for non-signal connections
2019-05-05 continue track
2019-05-05 pcb: track capacitors for zynq
2019-05-12 try to track 1st group data for ddr3.
2019-05-17 add VIN to 5V track
2019-05-19 fill pin delay for xc7z020
